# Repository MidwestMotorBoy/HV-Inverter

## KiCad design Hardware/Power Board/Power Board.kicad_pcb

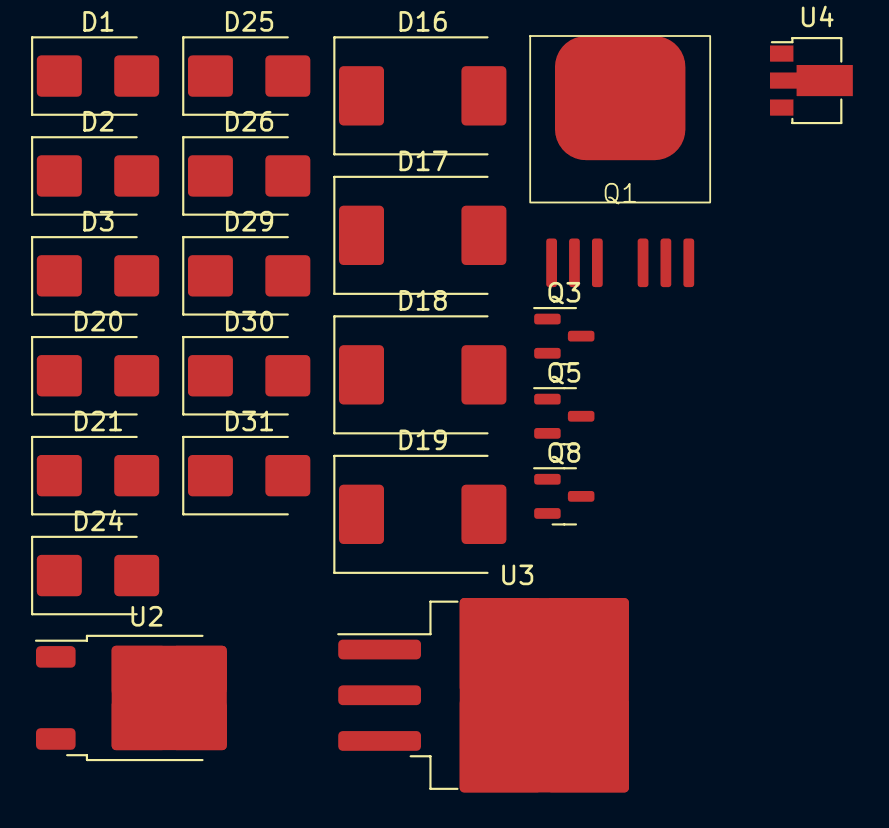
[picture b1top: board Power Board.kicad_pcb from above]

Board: 2 copper layers, 22 parts (0 on the bottom side), 13 nets, no tracks yet.

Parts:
D1, D2, D3, D24, D25, D26, D29, D30, D31: SM6T24A; D_SMB
D16, D17, D18, D19: SS36-E3/57T; D_SMC
D20, D21: 24V-550mW-SMB; D_SMB
Q1: NJFET; HYG050N13NS1B6
Q3, Q5, Q8: AO3400A; SOT-23
U2: L78M15; TO-252-2
U3: LM7905S; TO-263-3_TabPin2
U4: L78L33_SOT89; SOT-89-3

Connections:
/POWER_STAGE/FET_DRAIN: D1.1 (A1), D24.1 (A1), D29.1 (A1)
unnamed: D1.2 (A2), D2.1 (A1)
unnamed: D2.2 (A2), D3.1 (A1)
unnamed: D16.2 (A), D17.2 (A)
unnamed: D16.1 (K), D18.1 (K), D20.1 (K), U2.1 (IN)
unnamed: D17.1 (K), D19.1 (K), D21.1 (K), U3.2 (VI)
unnamed: D18.2 (A), D19.2 (A)
unnamed: D20.2 (A), D21.2 (A), U2.2 (GND), U3.1 (GND)
unnamed: D24.2 (A2), D25.1 (A1)
unnamed: D25.2 (A2), D26.1 (A1)
unnamed: D29.2 (A2), D30.1 (A1)
unnamed: D30.2 (A2), D31.1 (A1)
unnamed: Q3.2 (S), Q5.2 (S), Q8.2 (S), U3.3 (VO)

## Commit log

2023-04-07 Further Progress with pwoer stages and HV voltage sensing
2023-04-10 Updates to board, changed gate driver IC to one with external clamp
2023-04-11 Ditched ASC
2023-04-15 departure commit
2023-05-09 Board Layout Almost Done, about to remove Kelvin source due to concerns about uneven current sharing
2023-05-11 Finished intial LV board connector routing, going to tear up current sense and redo
2023-05-11 Current sense reroute
